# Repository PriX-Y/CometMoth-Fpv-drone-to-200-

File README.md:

My first FPV/Cinematic Dron design

There its some visual

this frame can be print in 2 case style . 
base:

filled v2

with honeycomb hole v1

top:

v2

v1 honeyocmb

v2 frame
wight more but look better(for me)
neee be full filled in 3d print to work
v2 top
its lighter then v2 but i think can be more weak
so need be full filled

v1 frame
hexagon base its lighter so better in air
same need be full filled
top v1
honeycomb top its to light and can be stronger
same 4 time need be full filled

filled need be to dont break when you crash
fillament need be PETG fillant but better use:
PA6CH12 if have money and good printer. i give later dfx file if someone wanna cut in carbon fiber

all how to conect frame is in Case Conecting pdf file

PETG must be used because other plastics and filaments cannot withstand the heat generated by the motors.

compoment like 
F4 V3 PLUS Flight Controller have all what 
ESC ( voltage controler) and flight controler 

SpeedyBee TX800 5.8GHz have anten so we dont need buy same like SpeedyBee TX800 5.8GHz

Emax RS2205-2300KV Motors its enough strong  to hold go pro so if you wand you can project for go pro holder and give to issue

My GPS modem use SAM-M8Q its so good chip becus dont need antena and its small 15x15mm. is all in one chip they need recistors and capacitors to filtr energy
i use kicad libray

to this 3d model i give this connections only for hole

NOTE:
to CNHL LiPo Battery 4S 14.8V 1300mAh you need special charger

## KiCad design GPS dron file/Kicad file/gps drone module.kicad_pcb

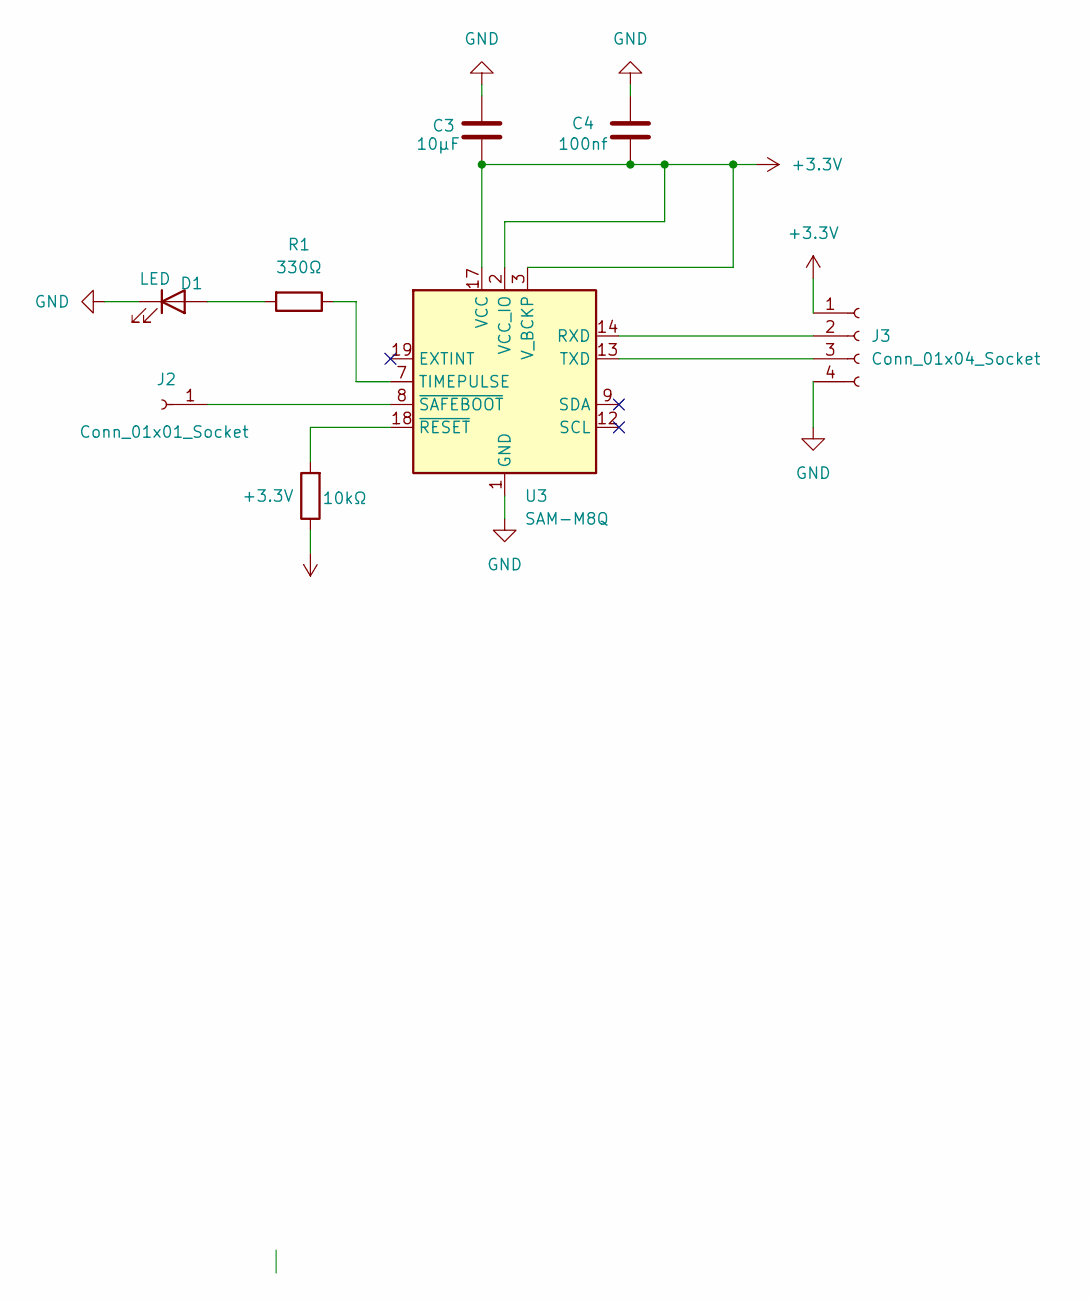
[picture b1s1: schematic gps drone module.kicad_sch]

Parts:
C3: 10µF; C_0805_2012Metric_Pad1.18x1.45mm_HandSolder
C4: 100nf; C_0805_2012Metric_Pad1.18x1.45mm_HandSolder
D1: LED; LED_0201_0603Metric_Pad0.64x0.40mm_HandSolder
J2: Conn_01x01_Socket; PinHeader_1x01_P1.00mm_Vertical
J3: Conn_01x04_Socket; Joint-Tech_C5080WR-04P_1x04_P5.08mm_Vertical
R1: 330Ω; R_0805_2012Metric_Pad1.20x1.40mm_HandSolder
R3: 10kΩ; R_0805_2012Metric_Pad1.20x1.40mm_HandSolder
U3: SAM-M8Q; ublox_SAM-M8Q

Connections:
+3.3V: C3.2, C4.2, J3.1, R3.1, U3.2 (VCC_IO), U3.3 (V_BCKP), U3.17 (VCC)
GND: C3.1, C4.1, D1.1 (K), J3.4, U3.1 (GND), U3.4 (GND), U3.5 (GND), U3.6 (GND), U3.10 (GND), U3.11 (GND), U3.15 (GND), U3.16 (GND), U3.20 (GND)
unnamed: D1.2 (A), R1.2
unnamed: J2.1, U3.8 (~SAFEBOOT)
unnamed: J3.2, U3.14 (RXD)
unnamed: J3.3, U3.13 (TXD)
unnamed: R1.1, U3.7 (TIMEPULSE)
unnamed: R3.2, U3.18 (~RESET)

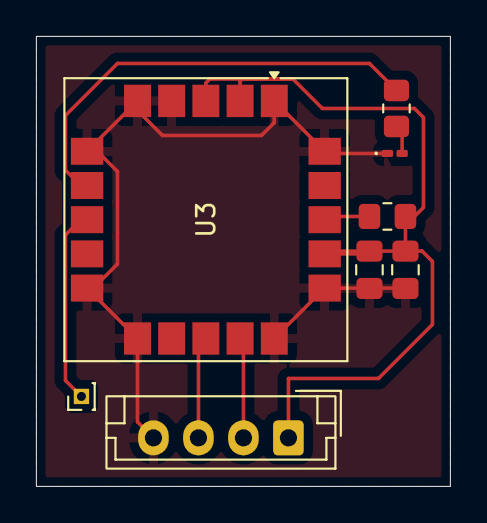
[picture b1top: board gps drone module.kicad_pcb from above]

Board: 2 copper layers, 23.0 x 25.0 mm, 8 parts (0 on the bottom side), 8 nets.

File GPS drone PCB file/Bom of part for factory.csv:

"Reference","Qty","Value","DNP","Exclude from BOM","Exclude from Board","Footprint","Datasheet"
"C3","1","10µF","","","","Capacitor_SMD:C_0805_2012Metric_Pad1.18x1.45mm_HandSolder","~"
"C4","1","100nf","","","","Capacitor_SMD:C_0805_2012Metric_Pad1.18x1.45mm_HandSolder","~"
"D1","1","LED","","","","LED_SMD:LED_0201_0603Metric_Pad0.64x0.40mm_HandSolder","~"
"J2","1","Conn_01x01_Socket","","","","Connector_PinHeader_1.00mm:PinHeader_1x01_P1.00mm_Vertical","~"
"J3","1","Conn_01x04_Socket","","","","Connector:Joint-Tech_C5080WR-04P_1x04_P5.08mm_Vertical","~"
"R1","1","330Ω","","","","Resistor_SMD:R_0805_2012Metric_Pad1.20x1.40mm_HandSolder","~"
"R3","1","10kΩ","","","","Resistor_SMD:R_0805_2012Metric_Pad1.20x1.40mm_HandSolder","~"
"U3","1","SAM-M8Q","","","","RF_GPS:ublox_SAM-M8Q","https://www.u-blox.com/sites/default/files/SAM-M8Q_DataSheet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"

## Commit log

2025-12-28 Revise version labels and add connection instructions
    Updated version references and clarified frame connection instructions.
2025-12-28 Enhance README with component and connection details
    Added additional details about components and connections.
2025-12-28 Revise Jonuary.md for clarity and add images
    Updated the content of Jonuary.md to improve clarity and structure, including additional images and corrections to text.
2025-12-28 Rename journal.md to journaly.md
2026-01-23 Rename FActoryFile.zip to FActoz
2026-01-23 Rename FActoz to
2026-01-23 Update Nothing Here
2026-01-25 Add 'its not main bom.txt' to BOM directory
2026-01-25 Update README with corrections and enhancements
    Corrected typos and improved clarity in the README.
2026-01-25 Revise drone project details and component updates
    Updated the journal to reflect changes in the drone concept, including the decision to switch from FPV to a cinematic style and the need for GPS. Added details about the components and parts sourcing.
2026-01-25 Revise drone project details and component list
    Updated the journal to reflect changes in the drone project, including the decision to switch from FPV to cinematic style, and detailed the components and costs involved.
2026-01-25 Fix grammar and spelling in README.md
    Corrected grammar and spelling in the README.
2026-01-25 Add BetaFlight app link and tutorial
    Added a link to the BetaFlight app and a YouTube tutorial for drone configuration.
2026-01-25 Update README with component details and image
    Added image and additional notes about components.
